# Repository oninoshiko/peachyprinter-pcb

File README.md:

This is just the production version of the Peachy Printer PCB, converted from Eagle format to Kicad.

Thanks to:

Rylan Grayston and the Peachy Team (for opening-sourceing, not just the 
					software, but the entire peachy design)

lachlanA (for the eagle to kicad conversion ULP)

Erich Heine (for the eagle half of the conversion)

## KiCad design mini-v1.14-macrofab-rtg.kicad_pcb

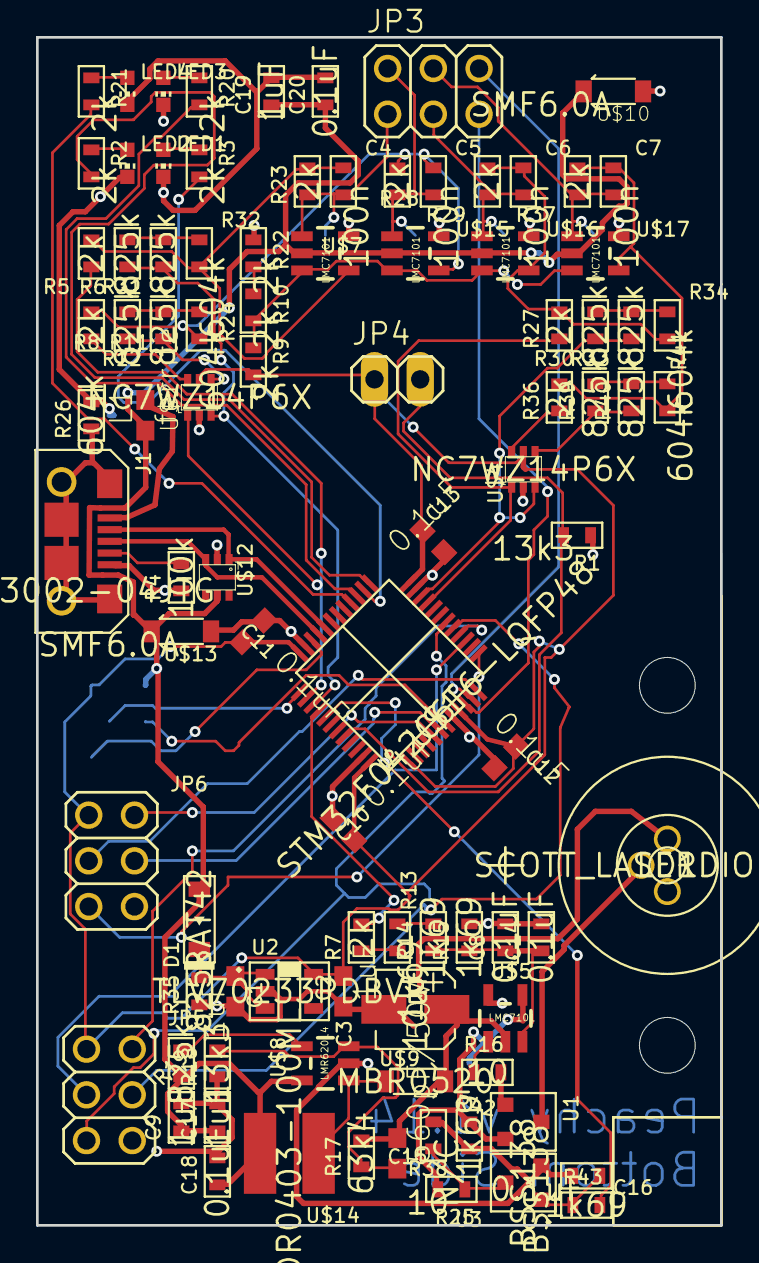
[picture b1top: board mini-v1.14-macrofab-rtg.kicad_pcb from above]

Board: 2 copper layers, 38.0 x 66.0 mm, 106 parts (0 on the bottom side), 67 nets.

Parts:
3V71: TPB1,27; B1,27
@HOLE0, @HOLE1: (no value)
C1, C2, C9, C17, C19: 1uF; C0603
C3: 10uF; CP4MM
C4, C5, C6, C7: 100n; C0603
C8, C10, C11, C12, C13, C14, C16, C18, C20: 0.1uF; C0603
C15: 560pF/50V; C0603
D1: BAT42; SOD-123
GND71: TPB1,27; B1,27
J1: MICROUSB-RIGHT
JP3, JP5, JP6: 2X03
JP4: 1X02
L1: ferrite; C0603
LASER71: TPB2,54; B2,54
LD1: SCOTT_LASERDIODELD3; SCOTT_LASERDIODE3
LED1, LED2, LED3, LED4: CHIP-LED0603
NRST71: TPB1,27; B1,27
R1, R18: 13k3; R0603
R2, R3, R5, R7, R8, R9, R10, R20, R21, R22, R23, R27, R28, R29, R36, R37: 2k; R0603
R4: 100k; R0603
R6, R11, R12, R19, R30, R31, R33, R35, R39, R40: 825k; R0603
R13, R14, R15, R38, R43: 1k69; R0603
R16, R25: 10; R0603
R17: 63k4; R0603
R24, R26, R32, R34, R41: 604k; R0603
R42: N/C; R0603
SWCLK71: TPB1,27; B1,27
SWDIO71: TPB1,27; B1,27
TP2: GND; B2,54
TP3, TP4, TP5, TP6: TPB1,27; B1,27
U1, U3: BSS138; SOT-23-3
U2: TLV70233PDBVR; SOT-23-5
U$1: STM32F042C6T6-LQFP48; LQFP48
U$2, U$4: NC7WZ14P6X; SC70-6
U$5, U$7, U$15, U$16, U$17: LMC7101; SOT23-5
U$8: LMR62014; SOT23-5
U$9: MBR0520; SOD123
U$10, U$13: SMF6.0A; SOD123
U$12: SP3002-04JTG; SC70-6
U$14: SDR0403-100ML; SDR0403
VUSB71: TPB1,27; B1,27

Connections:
3V: 3V71.TP, C2.2, C9.P$1, C10.1, C11.1, C12.1, C13.1, C17.P$1, C18.P$1, C19.P$1, C20.P$1, D1.ANOD, JP4.1, JP5.1, JP6.1, L1.1, R9.P$2, R19.P$1, U2.P$5, U$1.P1, U$1.P9, U$1.P24, U$1.P36, U$1.P48, U$2.P5, U$4.P5, U$7.2, U$8.5, U$10.CATH, U$12.P5, U$13.CATH, U$14.P$1, U$15.2, U$16.2, U$17.2, VUSB71.TP
/mini-v1.14-macrofab-rtg_SS_1/N$2: R2.P$2, U$1.P25
/mini-v1.14-macrofab-rtg_SS_1/N$3: LED2.A, R2.P$1
/mini-v1.14-macrofab-rtg_SS_1/N$4: C1.1, D1.CATH, R35.P$2, U2.P$1, U2.P$3
/mini-v1.14-macrofab-rtg_SS_1/N$5: J1.4, R4.P$2
/mini-v1.14-macrofab-rtg_SS_1/N$12: LED1.A, R3.P$1
/mini-v1.14-macrofab-rtg_SS_1/N$13: R3.P$2, U$1.P26
/mini-v1.14-macrofab-rtg_SS_1/N$14: J1.1, L1.2
/mini-v1.14-macrofab-rtg_SS_1/N$24: LED3.A, R20.P$1
/mini-v1.14-macrofab-rtg_SS_1/N$27: LED4.A, R21.P$1
/mini-v1.14-macrofab-rtg_SS_1/N$28: R20.P$2, U$1.P27
/mini-v1.14-macrofab-rtg_SS_1/N$29: R21.P$2, U$1.P28
/mini-v1.14-macrofab-rtg_SS_1/USB_DM: J1.2, U$1.P32, U$12.P1
/mini-v1.14-macrofab-rtg_SS_1/USB_DP: J1.3, U$1.P33, U$12.P3
/mini-v1.14-macrofab-rtg_SS_2/2V2: R9.P$1, R10.P$2, U$7.3, U$15.3, U$16.3, U$17.3
/mini-v1.14-macrofab-rtg_SS_2/COARSE1: R8.P$1, U$2.P6
/mini-v1.14-macrofab-rtg_SS_2/FINE1: R11.P$1, R12.P$1, U$2.P4
/mini-v1.14-macrofab-rtg_SS_2/FINE3: R39.P$1, R40.P$1, U$4.P4
/mini-v1.14-macrofab-rtg_SS_2/N$7: R36.P$1, U$4.P6
/mini-v1.14-macrofab-rtg_SS_2/N$8: R11.P$2, R12.P$2, R24.P$1
/mini-v1.14-macrofab-rtg_SS_2/N$10: C5.P$1, R8.P$2, R24.P$2, R28.P$2, U$15.4
/mini-v1.14-macrofab-rtg_SS_2/N$22: R10.P$1, R22.P$2
/mini-v1.14-macrofab-rtg_SS_2/N$30: R30.P$2, R33.P$2, R34.P$1
/mini-v1.14-macrofab-rtg_SS_2/N$31: R6.P$2, R31.P$2, R32.P$1
/mini-v1.14-macrofab-rtg_SS_2/N$32: C6.P$1, R27.P$2, R29.P$2, R34.P$2, U$16.4
/mini-v1.14-macrofab-rtg_SS_2/N$35: R39.P$2, R40.P$2, R41.P$1
/mini-v1.14-macrofab-rtg_SS_2/N$36: C7.P$1, R36.P$2, R37.P$2, R41.P$2, U$17.4
/mini-v1.14-macrofab-rtg_SS_2/OUT: C4.P$2, JP3.1, R23.P$1, TP3.TP, U$7.1
/mini-v1.14-macrofab-rtg_SS_2/OUT1: C5.P$2, JP3.2, R28.P$1, TP4.TP, U$15.1
/mini-v1.14-macrofab-rtg_SS_2/OUT2: C6.P$2, JP3.3, R29.P$1, TP5.TP, U$16.1
/mini-v1.14-macrofab-rtg_SS_2/OUT3: C7.P$2, JP3.4, R37.P$1, TP6.TP, U$17.1
/mini-v1.14-macrofab-rtg_SS_2/XSUM: C4.P$1, R5.P$2, R23.P$2, R32.P$2, U$7.4
/mini-v1.14-macrofab-rtg_SS_3/6V: C3.P$1, C15.2, LD1.P$1, R17.P$2, U$5.2, U$9.CATH
/mini-v1.14-macrofab-rtg_SS_3/N$1: R25.P$1, R42.P$2, U3.P$3
/mini-v1.14-macrofab-rtg_SS_3/N$6: R7.P$1, R13.P$2
/mini-v1.14-macrofab-rtg_SS_3/N$9: R13.P$1, R14.P$2
/mini-v1.14-macrofab-rtg_SS_3/N$11: C8.P$1, C14.P$1, R14.P$1, R15.P$1, U$5.3
/mini-v1.14-macrofab-rtg_SS_3/N$15: U$8.1, U$9.ANOD, U$14.P$2
/mini-v1.14-macrofab-rtg_SS_3/N$16: LD1.P$3, U1.P$3
/mini-v1.14-macrofab-rtg_SS_3/N$17: LASER71.TP, R25.P$2, R38.P$2, U1.P$2, U$5.4
/mini-v1.14-macrofab-rtg_SS_3/N$19: R16.P$2, U1.P$1
/mini-v1.14-macrofab-rtg_SS_3/N$20: R16.P$1, U$5.1
/mini-v1.14-macrofab-rtg_SS_3/N$21: C16.P$1, R43.P$1, U3.P$1
/mini-v1.14-macrofab-rtg_SS_3/N$25: C15.1, R17.P$1, R18.P$2, U$8.3
/mini-v1.14-macrofab-rtg_SS_3/N$26: R19.P$2, U$8.4
ADC0: JP3.5, U$1.P10
ADC1: JP3.6, U$1.P11
ADC2: JP6.3, U$1.P12
ADC3: JP6.5, U$1.P13
BOOT0: JP4.2, R1.P$2, U$1.P44
GND: C1.2, C2.1, C3.P$2, C8.P$2, C9.P$2, C10.2, C11.2, C12.2, C13.2, C14.P$2, C16.P$2, C17.P$2, C18.P$2, C19.P$2, C20.P$2, GND71.TP, J1.5, JP5.6, JP6.6, LED1.C, LED2.C, LED3.C, LED4.C, R1.P$1, R4.P$1, R15.P$2, R18.P$1, R22.P$1, R26.P$2, R35.P$1, R38.P$1, R42.P$1, TP2.TP, U2.P$2, U3.P$2, U$1.P8, U$1.P23, U$1.P35, U$1.P47, U$2.P2, U$4.P2, U$5.5, U$7.5, U$8.2, U$10.ANOD, U$12.P2, U$13.ANOD, U$15.5, U$16.5, U$17.5
LASER_EN: R43.P$2, U$1.P41
LASER_PWM_IN: R7.P$2, U$1.P40
MISO: JP5.2, U$1.P16
MOSI: JP5.4, U$1.P17
NRST: NRST71.TP, U$1.P7
SCK: JP5.3, U$1.P15
SCL: JP6.4, U$1.P6
SDA: JP6.2, U$1.P5
SLD: J1.S1, J1.S2, J1.S3, J1.S4, J1.S5, J1.S6, R26.P$1
SPI_CS: JP5.5, U$1.P18
SWCLK: SWCLK71.TP, U$1.P37
SWDIO: SWDIO71.TP, U$1.P34
XCOARSE_IN: R5.P$1, U$1.P38, U$2.P1
XFINE_IN: R6.P$1, R31.P$1, U$1.P39, U$2.P3
YCOARSE_IN: R27.P$1, U$1.P21, U$4.P1
YFINE_IN: R30.P$1, R33.P$1, U$1.P22, U$4.P3

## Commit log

2016-05-28 trim down to JUST 1.14 and convert to Kicad format
2016-05-28 mark unattached pins
2016-05-28 added .gitignore and fixed README.md
2016-05-28 footprints assigned
2016-05-28 Netlist generated and applied
